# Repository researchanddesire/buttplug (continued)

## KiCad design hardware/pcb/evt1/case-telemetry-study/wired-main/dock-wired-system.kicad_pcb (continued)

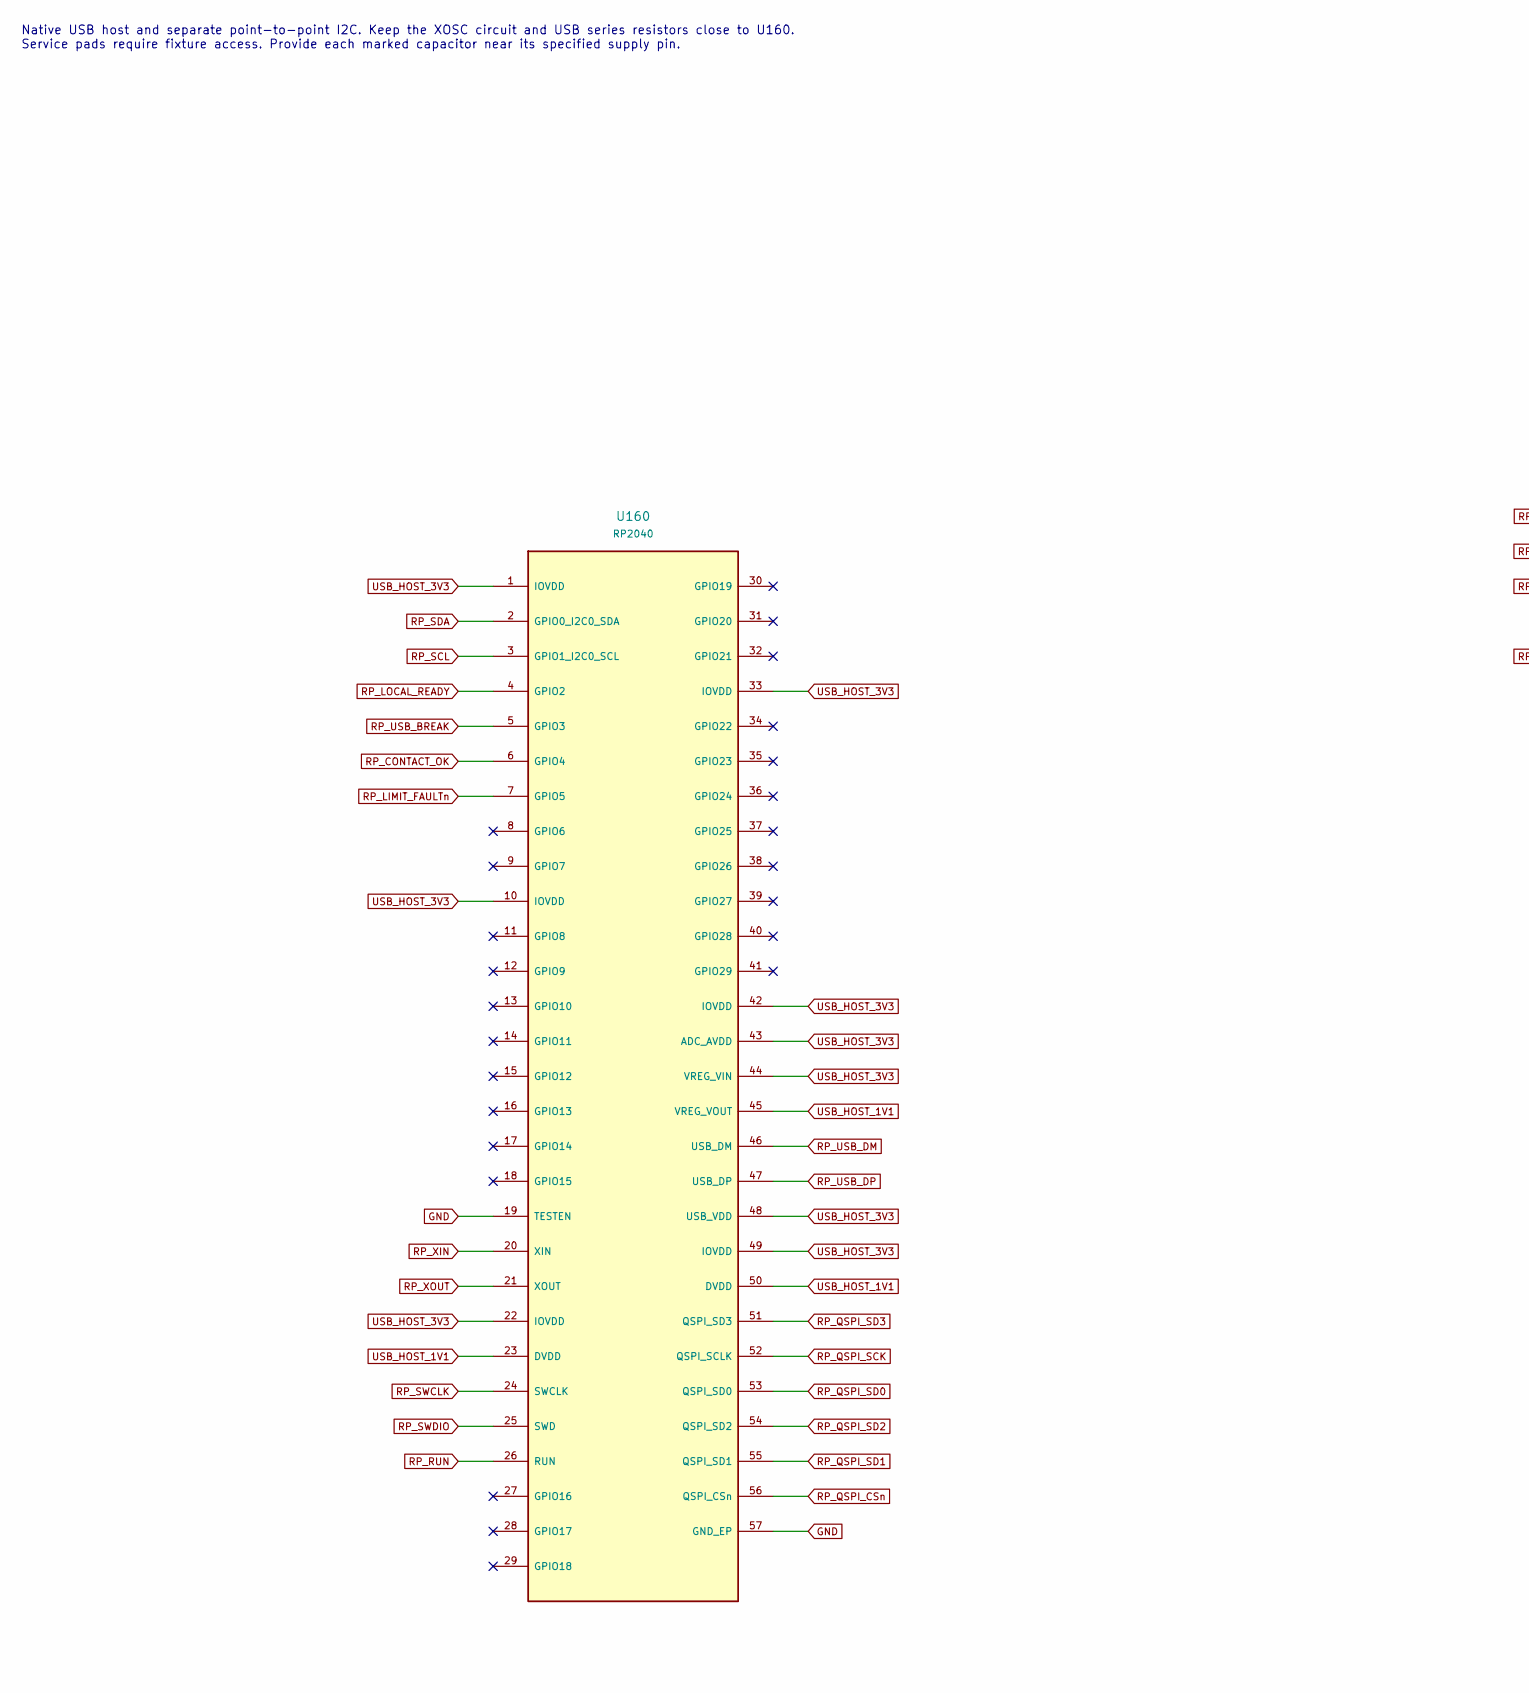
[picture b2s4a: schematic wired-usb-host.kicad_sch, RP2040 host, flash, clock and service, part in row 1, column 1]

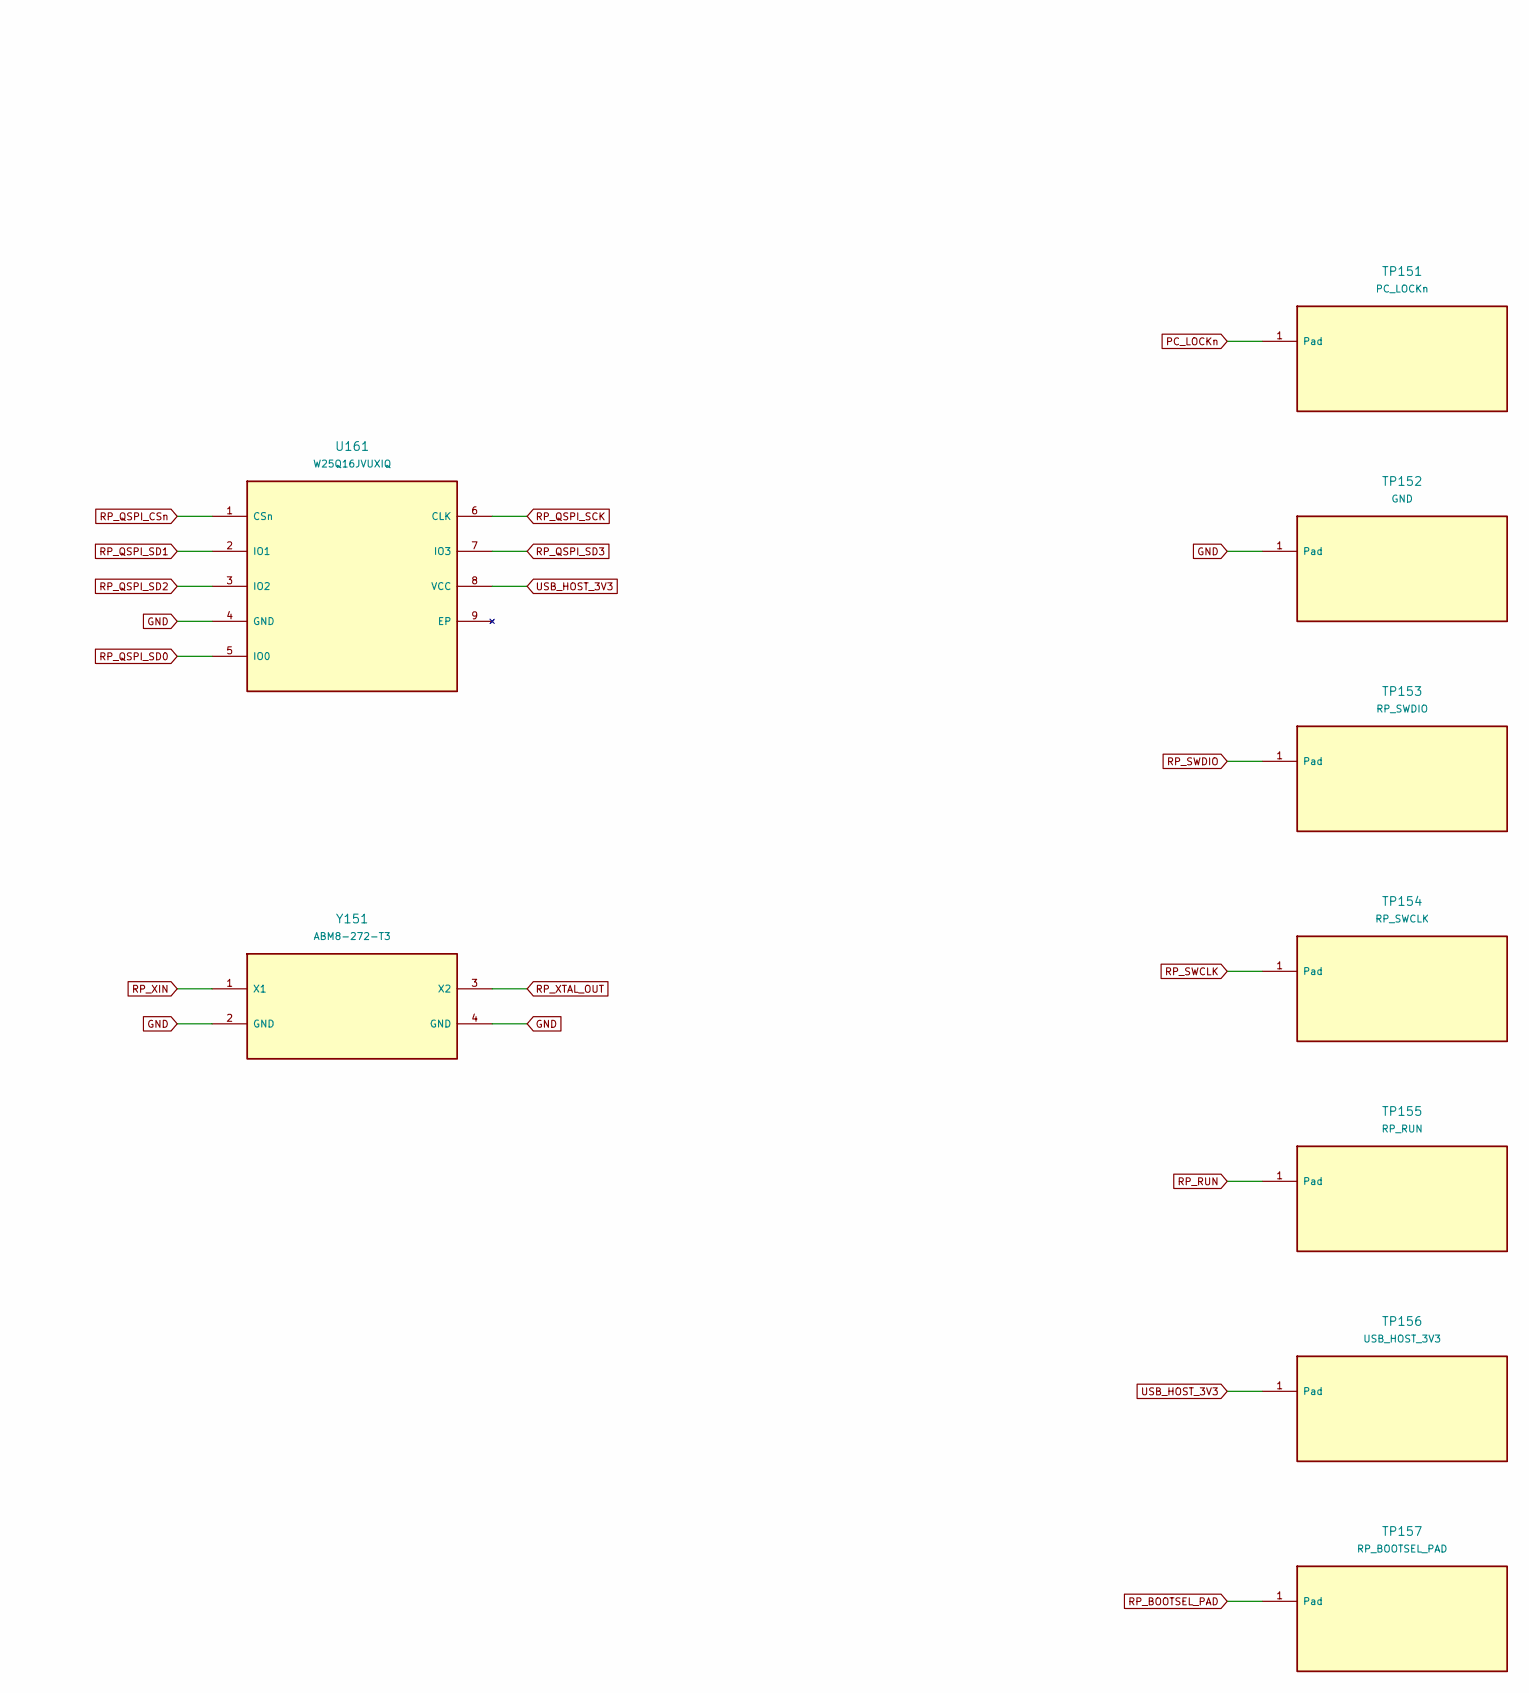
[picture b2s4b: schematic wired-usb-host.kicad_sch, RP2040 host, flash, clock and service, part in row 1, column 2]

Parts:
TP151: PC_LOCKn; TestPoint_Pad_D1.5mm
TP152: GND; TestPoint_Pad_D1.5mm
TP153: RP_SWDIO; TestPoint_Pad_D1.5mm
TP154: RP_SWCLK; TestPoint_Pad_D1.5mm
TP155: RP_RUN; TestPoint_Pad_D1.5mm
TP156: USB_HOST_3V3; TestPoint_Pad_D1.5mm
TP157: RP_BOOTSEL_PAD; TestPoint_Pad_D1.5mm
U160: RP2040; QFN-56-1EP_7x7mm_P0.4mm_EP3.2x3.2mm; MPN RP2040
U161: W25Q16JVUXIQ; Winbond_USON-8_2x3mm_P0.5mm_UX; MPN W25Q16JVUXIQ
Y151: ABM8-272-T3; Crystal_SMD_3225-4Pin_3.2x2.5mm; MPN ABM8-272-T3

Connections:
GND: TP152.1, U160.19 (TESTEN), U160.57 (GND_EP), U161.4 (GND), Y151.2 (GND), Y151.4 (GND); also elsewhere on the board
PC_LOCKn: TP151.1; also elsewhere on the board
RP_BOOTSEL_PAD: TP157.1; also elsewhere on the board
RP_CONTACT_OK: U160.6 (GPIO4); also elsewhere on the board
RP_LIMIT_FAULTn: U160.7 (GPIO5); also elsewhere on the board
RP_LOCAL_READY: U160.4 (GPIO2); also elsewhere on the board
RP_QSPI_CSn: U160.56 (QSPI_CSn), U161.1 (CSn); also elsewhere on the board
RP_QSPI_SCK: U160.52 (QSPI_SCLK), U161.6 (CLK)
RP_QSPI_SD0: U160.53 (QSPI_SD0), U161.5 (IO0)
RP_QSPI_SD1: U160.55 (QSPI_SD1), U161.2 (IO1)
RP_QSPI_SD2: U160.54 (QSPI_SD2), U161.3 (IO2)
RP_QSPI_SD3: U160.51 (QSPI_SD3), U161.7 (IO3)
RP_RUN: TP155.1, U160.26 (RUN); also elsewhere on the board
RP_SCL: U160.3 (GPIO1_I2C0_SCL); also elsewhere on the board
RP_SDA: U160.2 (GPIO0_I2C0_SDA); also elsewhere on the board
RP_SWCLK: TP154.1, U160.24 (SWCLK)
RP_SWDIO: TP153.1, U160.25 (SWD)
RP_USB_BREAK: U160.5 (GPIO3); also elsewhere on the board
RP_USB_DM: U160.46 (USB_DM); also elsewhere on the board
RP_USB_DP: U160.47 (USB_DP); also elsewhere on the board
RP_XIN: U160.20 (XIN), Y151.1 (X1); also elsewhere on the board
RP_XOUT: U160.21 (XOUT); also elsewhere on the board
RP_XTAL_OUT: Y151.3 (X2); also elsewhere on the board
USB_HOST_1V1: U160.23 (DVDD), U160.45 (VREG_VOUT), U160.50 (DVDD); also elsewhere on the board
USB_HOST_3V3: TP156.1, U160.1 (IOVDD), U160.10 (IOVDD), U160.22 (IOVDD), U160.33 (IOVDD), U160.42 (IOVDD), U160.43 (ADC_AVDD), U160.44 (VREG_VIN), U160.48 (USB_VDD), U160.49 (IOVDD), U161.8 (VCC); also elsewhere on the board

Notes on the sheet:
Native USB host and separate point-to-point I2C. Keep the XOSC circuit and USB series resistors close to U160. Service pads require fixture access. Provide each marked capacitor near its specified supply pin.

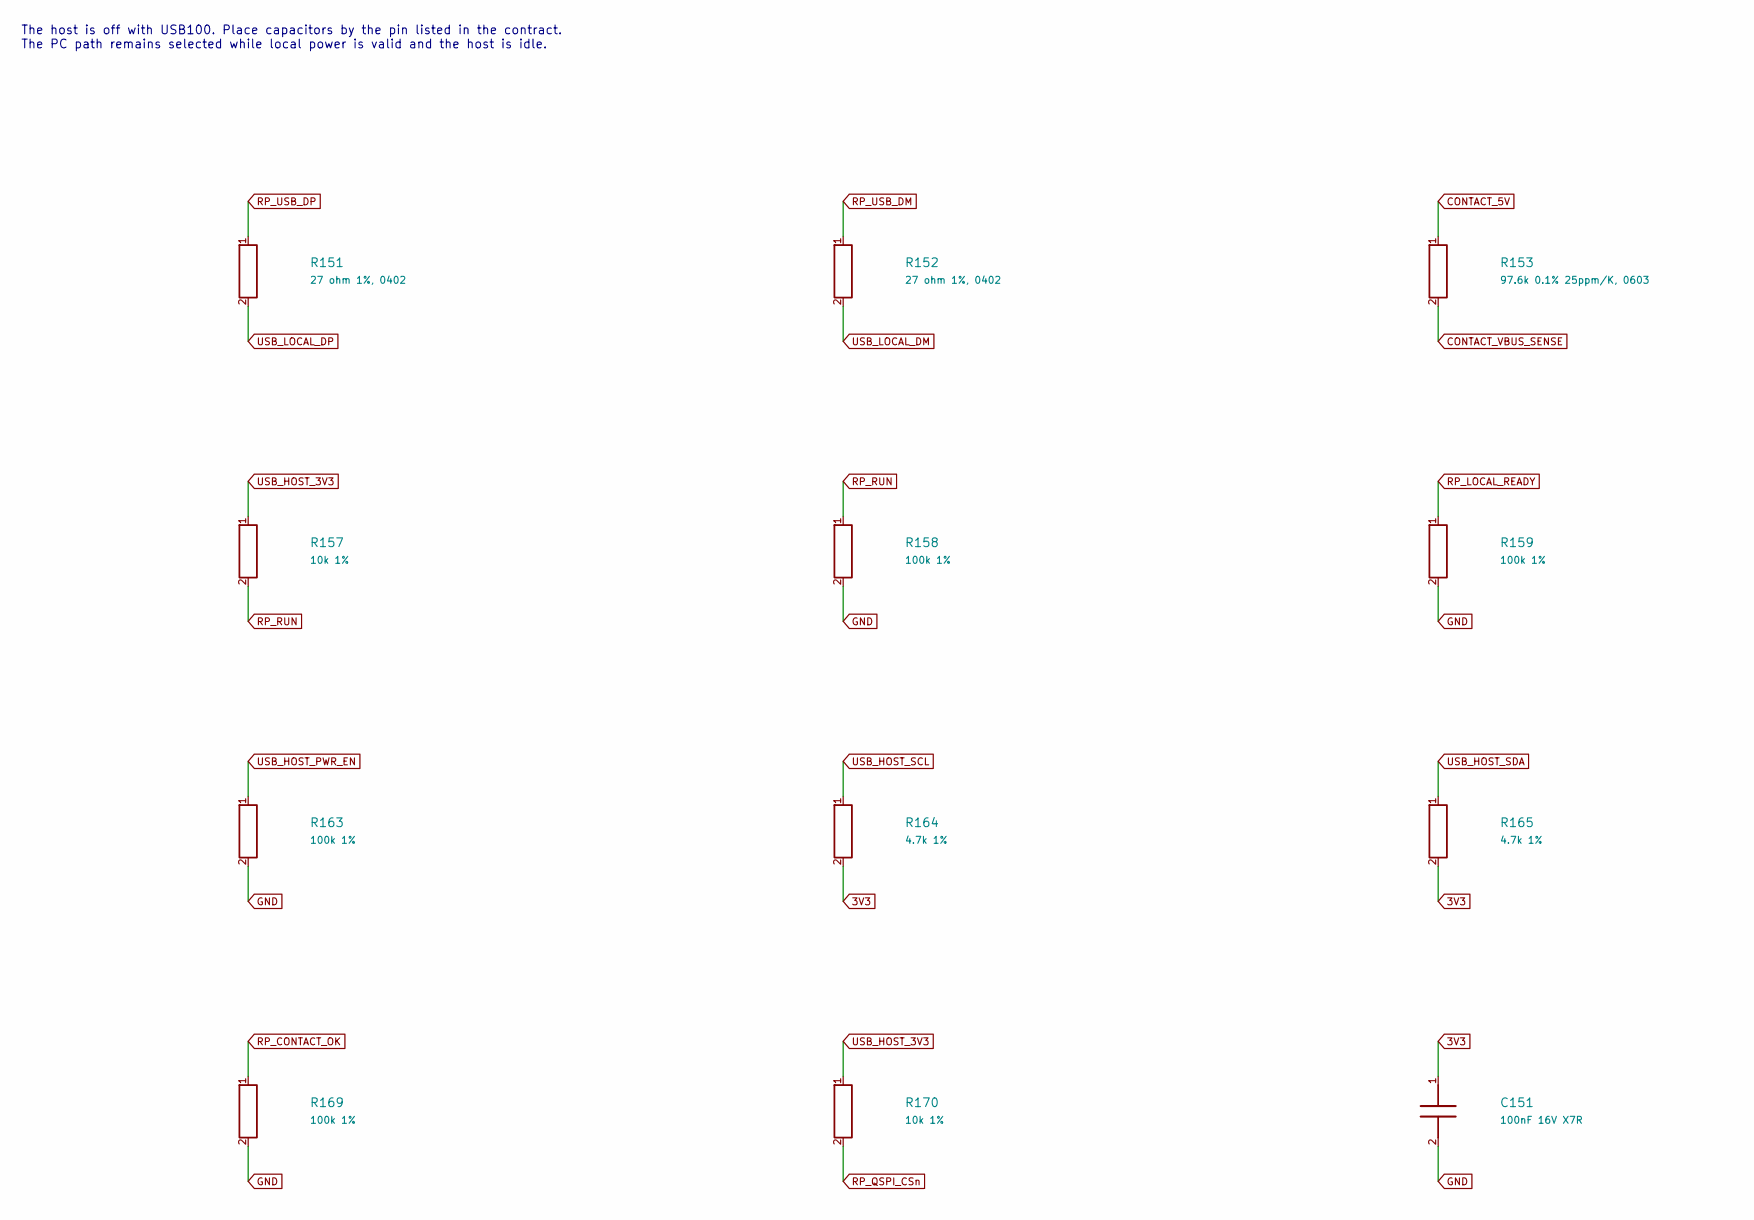
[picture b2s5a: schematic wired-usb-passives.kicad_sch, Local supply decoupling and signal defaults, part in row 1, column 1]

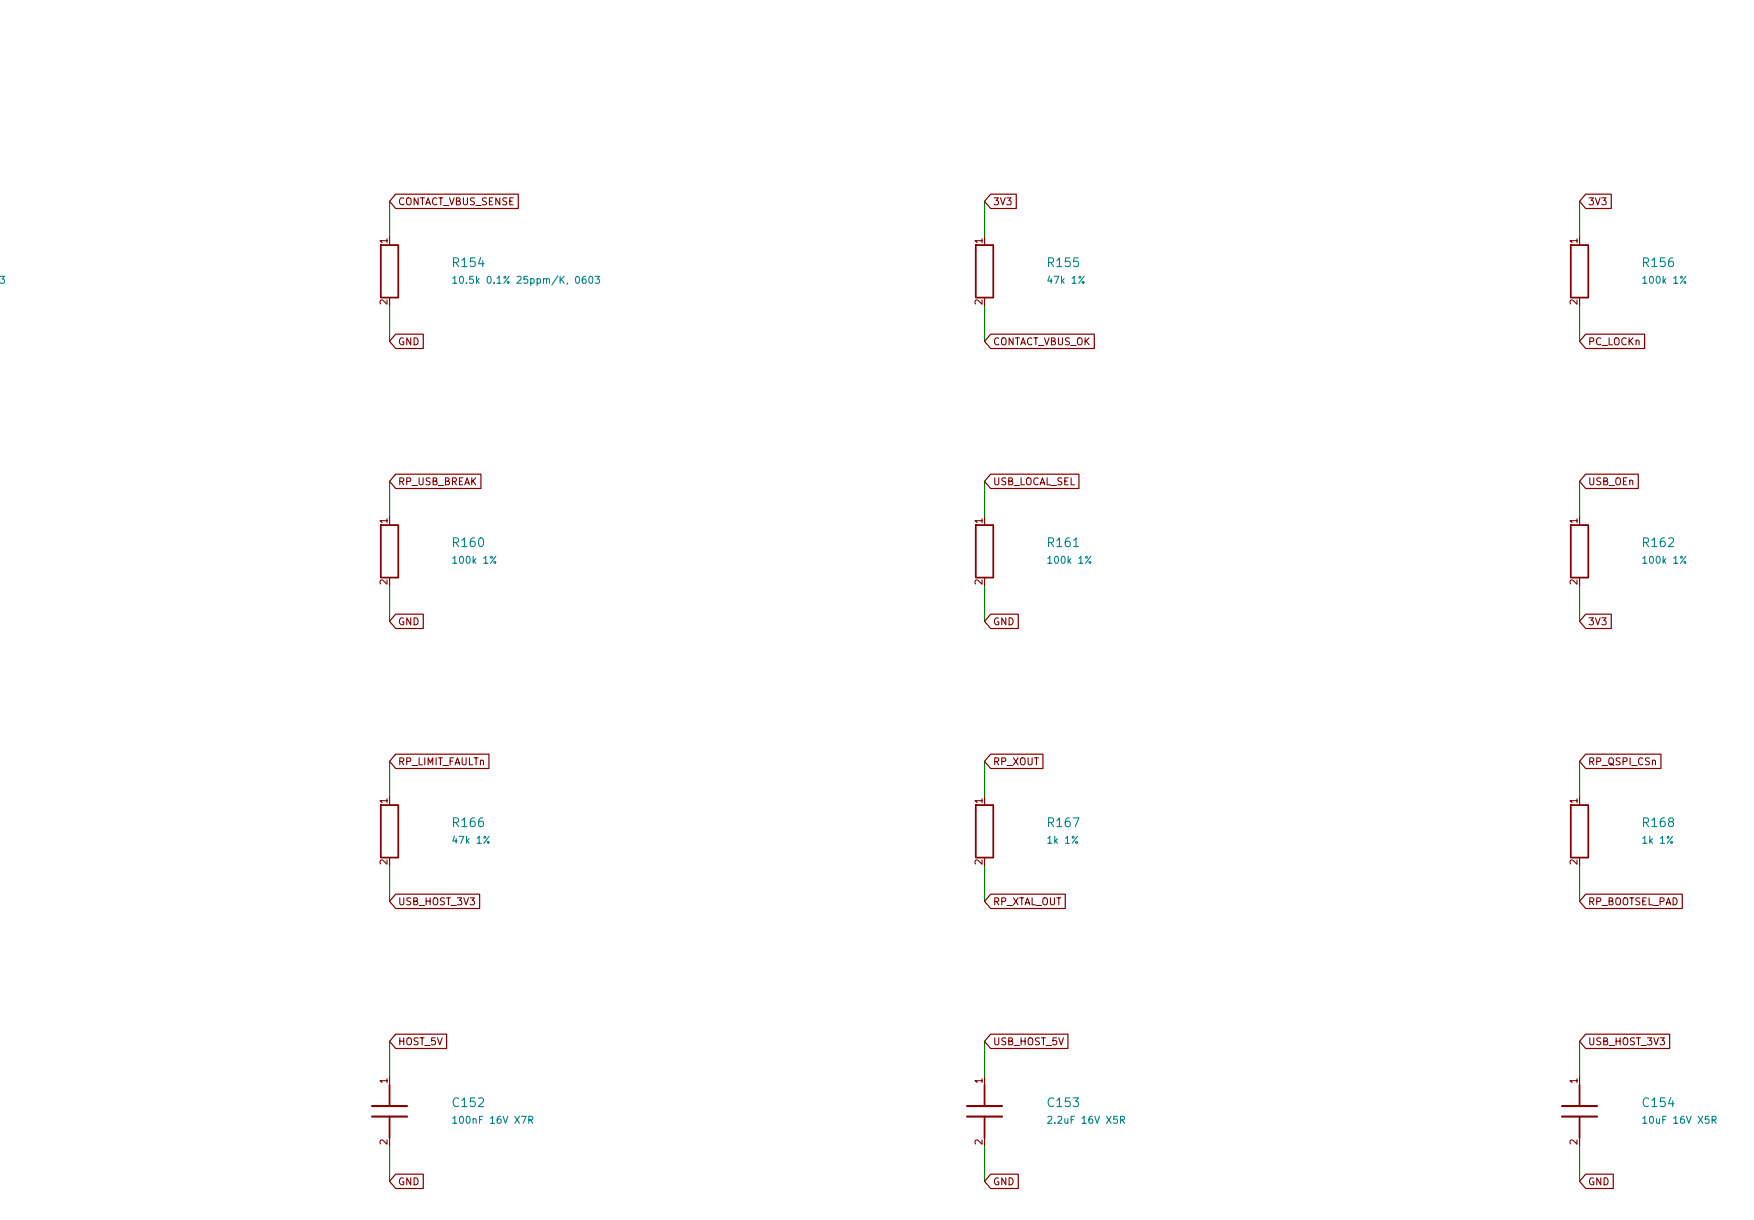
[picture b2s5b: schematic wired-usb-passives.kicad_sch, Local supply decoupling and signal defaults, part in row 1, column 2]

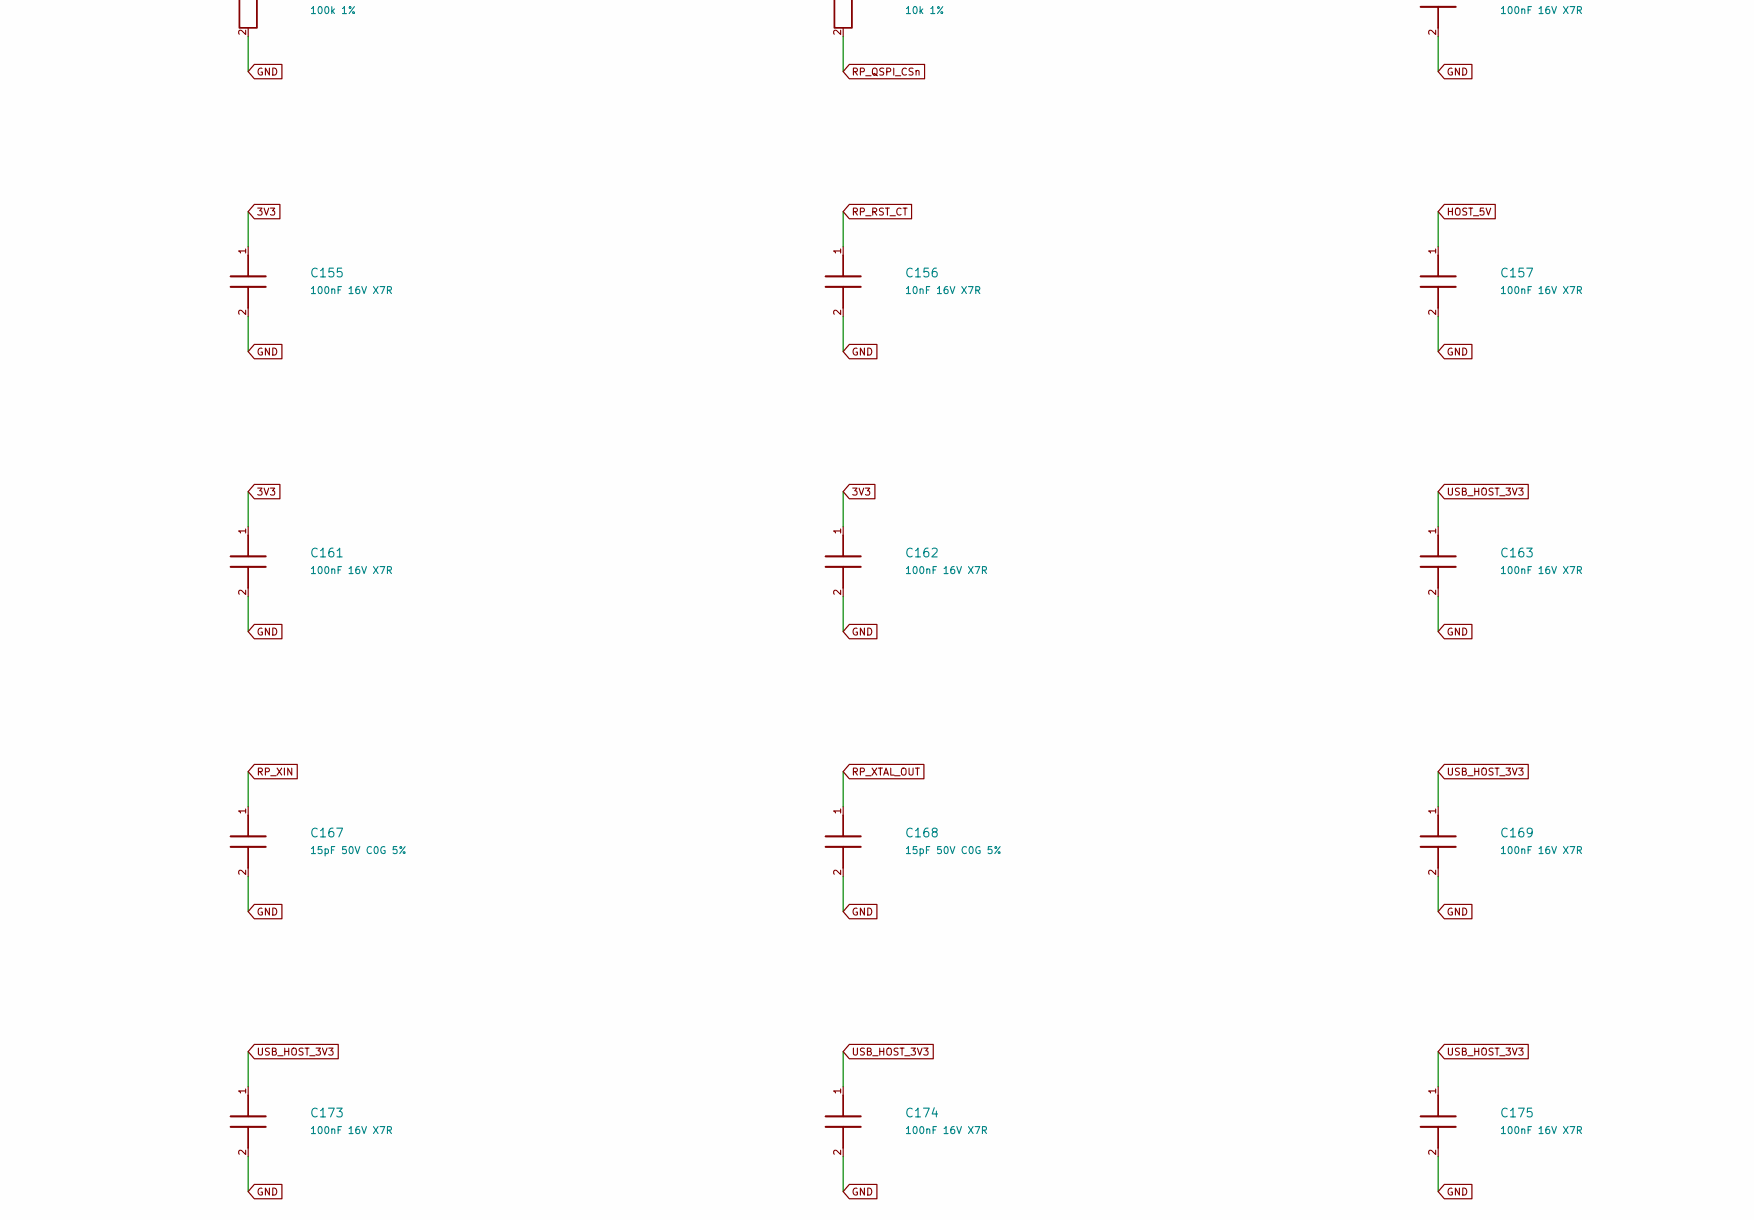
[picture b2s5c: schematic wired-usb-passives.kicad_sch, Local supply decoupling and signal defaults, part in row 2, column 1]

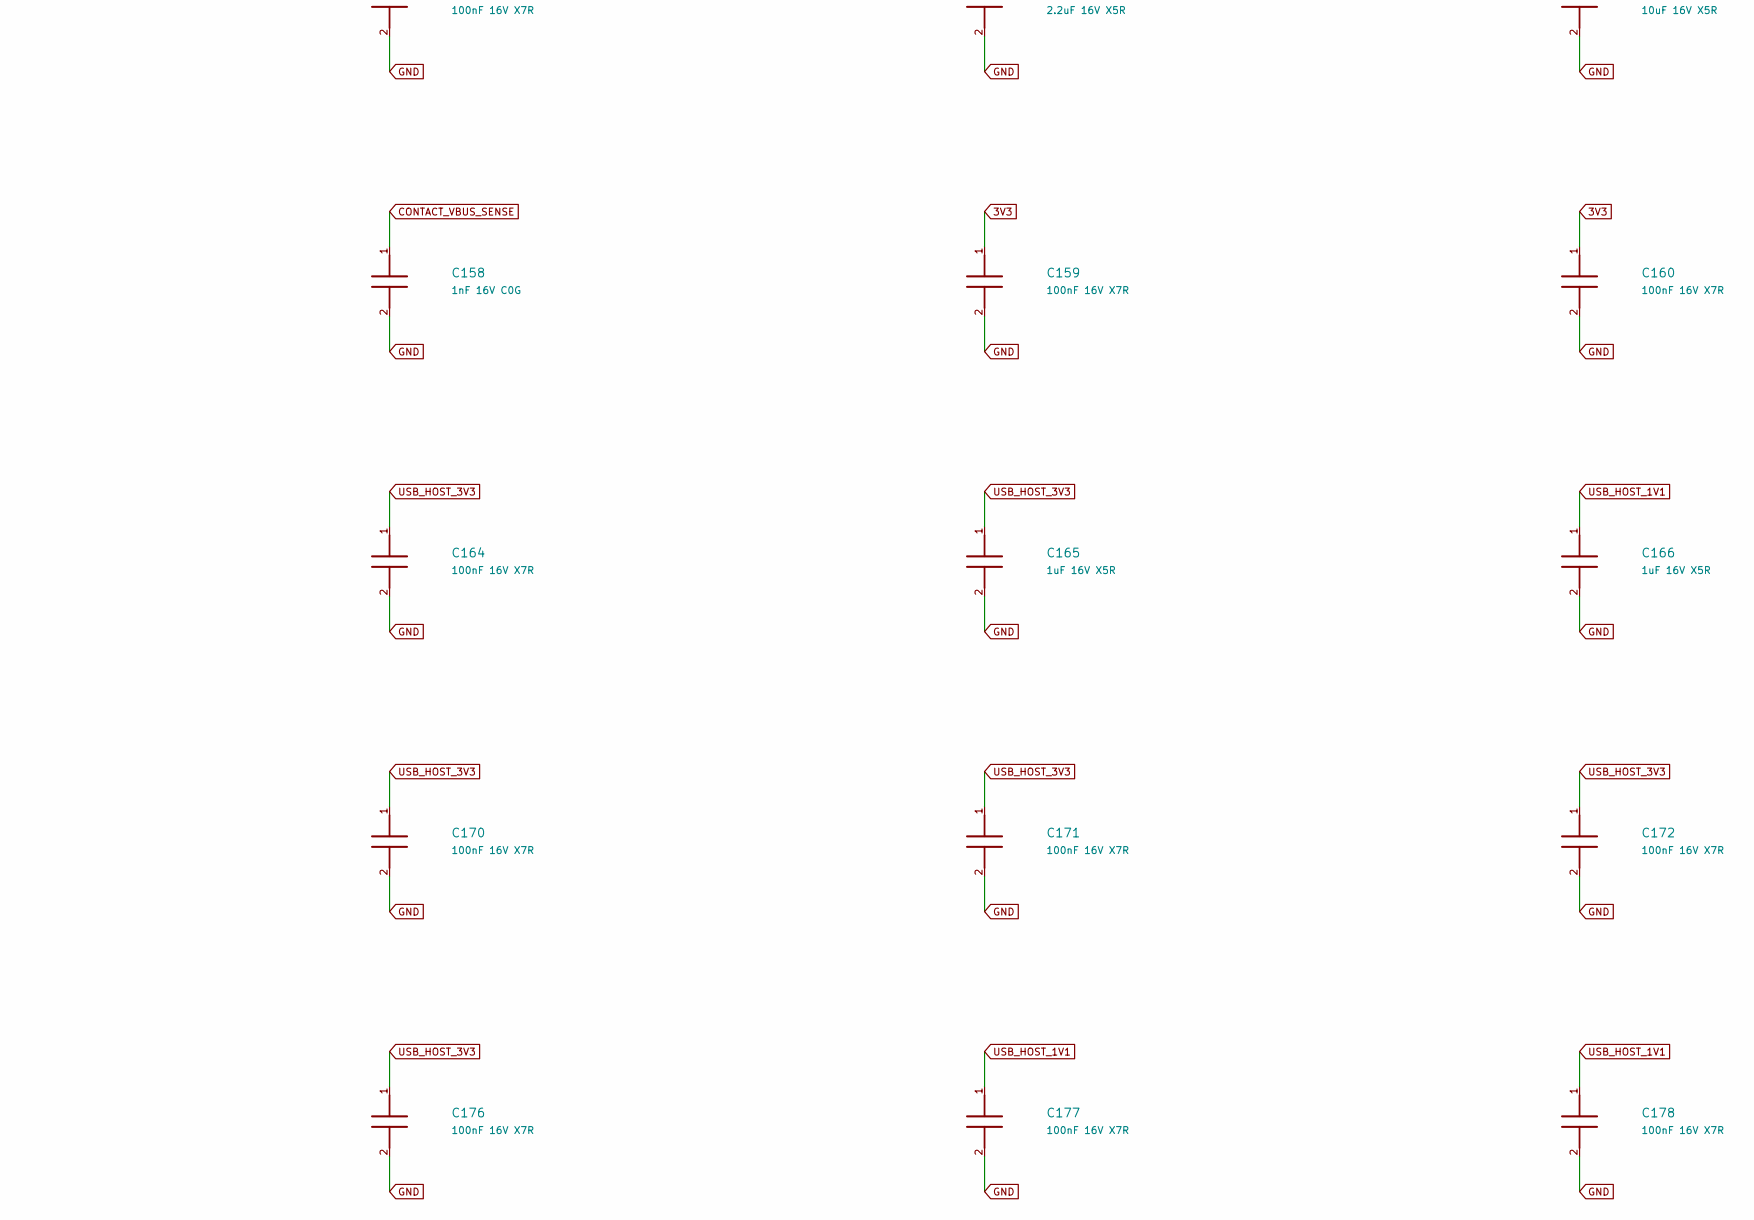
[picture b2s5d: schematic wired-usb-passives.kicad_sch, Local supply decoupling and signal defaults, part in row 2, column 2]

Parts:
C151, C152, C155, C157, C159, C160, C161, C162, C163, C164, C169, C170, C171, C172, C173, C174, C175, C176, C177, C178: 100nF 16V X7R; C_0402_1005Metric
C153: 2.2uF 16V X5R; C_0603_1608Metric
C154: 10uF 16V X5R; C_0805_2012Metric
C156: 10nF 16V X7R; C_0402_1005Metric
C158: 1nF 16V C0G; C_0402_1005Metric
C165, C166: 1uF 16V X5R; C_0603_1608Metric
C167, C168: 15pF 50V C0G 5%; C_0402_1005Metric
R151, R152: 27 ohm 1%, 0402; R_0402_1005Metric
R153: 97.6k 0.1% 25ppm/K, 0603; R_0603_1608Metric
R154: 10.5k 0.1% 25ppm/K, 0603; R_0603_1608Metric
R155, R166: 47k 1%; R_0402_1005Metric
R156, R158, R159, R160, R161, R162, R163, R169: 100k 1%; R_0402_1005Metric
R157, R170: 10k 1%; R_0402_1005Metric
R164, R165: 4.7k 1%; R_0402_1005Metric
R167, R168: 1k 1%; R_0402_1005Metric

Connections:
3V3: C151.1, C155.1, C159.1, C160.1, C161.1, C162.1, R155.1, R156.1, R162.2, R164.2, R165.2; also elsewhere on the board
CONTACT_5V: R153.1; also elsewhere on the board
CONTACT_VBUS_OK: R155.2; also elsewhere on the board
CONTACT_VBUS_SENSE: C158.1, R153.2, R154.1; also elsewhere on the board
GND: C151.2, C152.2, C153.2, C154.2, C155.2, C156.2, C157.2, C158.2, C159.2, C160.2, C161.2, C162.2, C163.2, C164.2, C165.2, C166.2, C167.2, C168.2, C169.2, C170.2, C171.2, C172.2, C173.2, C174.2, C175.2, C176.2, C177.2, C178.2, R154.2, R158.2, R159.2, R160.2, R161.2, R163.2, R169.2; also elsewhere on the board
HOST_5V: C152.1, C157.1; also elsewhere on the board
PC_LOCKn: R156.2; also elsewhere on the board
RP_BOOTSEL_PAD: R168.2; also elsewhere on the board
RP_CONTACT_OK: R169.1; also elsewhere on the board
RP_LIMIT_FAULTn: R166.1; also elsewhere on the board
RP_LOCAL_READY: R159.1; also elsewhere on the board
RP_QSPI_CSn: R168.1, R170.2; also elsewhere on the board
RP_RST_CT: C156.1; also elsewhere on the board
RP_RUN: R157.2, R158.1; also elsewhere on the board
RP_USB_BREAK: R160.1; also elsewhere on the board
RP_USB_DM: R152.1; also elsewhere on the board
RP_USB_DP: R151.1; also elsewhere on the board
RP_XIN: C167.1; also elsewhere on the board
RP_XOUT: R167.1; also elsewhere on the board
RP_XTAL_OUT: C168.1, R167.2; also elsewhere on the board
USB_HOST_1V1: C166.1, C177.1, C178.1; also elsewhere on the board
USB_HOST_3V3: C154.1, C163.1, C164.1, C165.1, C169.1, C170.1, C171.1, C172.1, C173.1, C174.1, C175.1, C176.1, R157.1, R166.2, R170.1; also elsewhere on the board
USB_HOST_5V: C153.1; also elsewhere on the board
USB_HOST_PWR_EN: R163.1; also elsewhere on the board
USB_HOST_SCL: R164.1; also elsewhere on the board
USB_HOST_SDA: R165.1; also elsewhere on the board
USB_LOCAL_DM: R152.2; also elsewhere on the board
USB_LOCAL_DP: R151.2; also elsewhere on the board
USB_LOCAL_SEL: R161.1; also elsewhere on the board
USB_OEn: R162.1; also elsewhere on the board

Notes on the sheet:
The host is off with USB100. Place capacitors by the pin listed in the contract. The PC path remains selected while local power is valid and the host is idle.

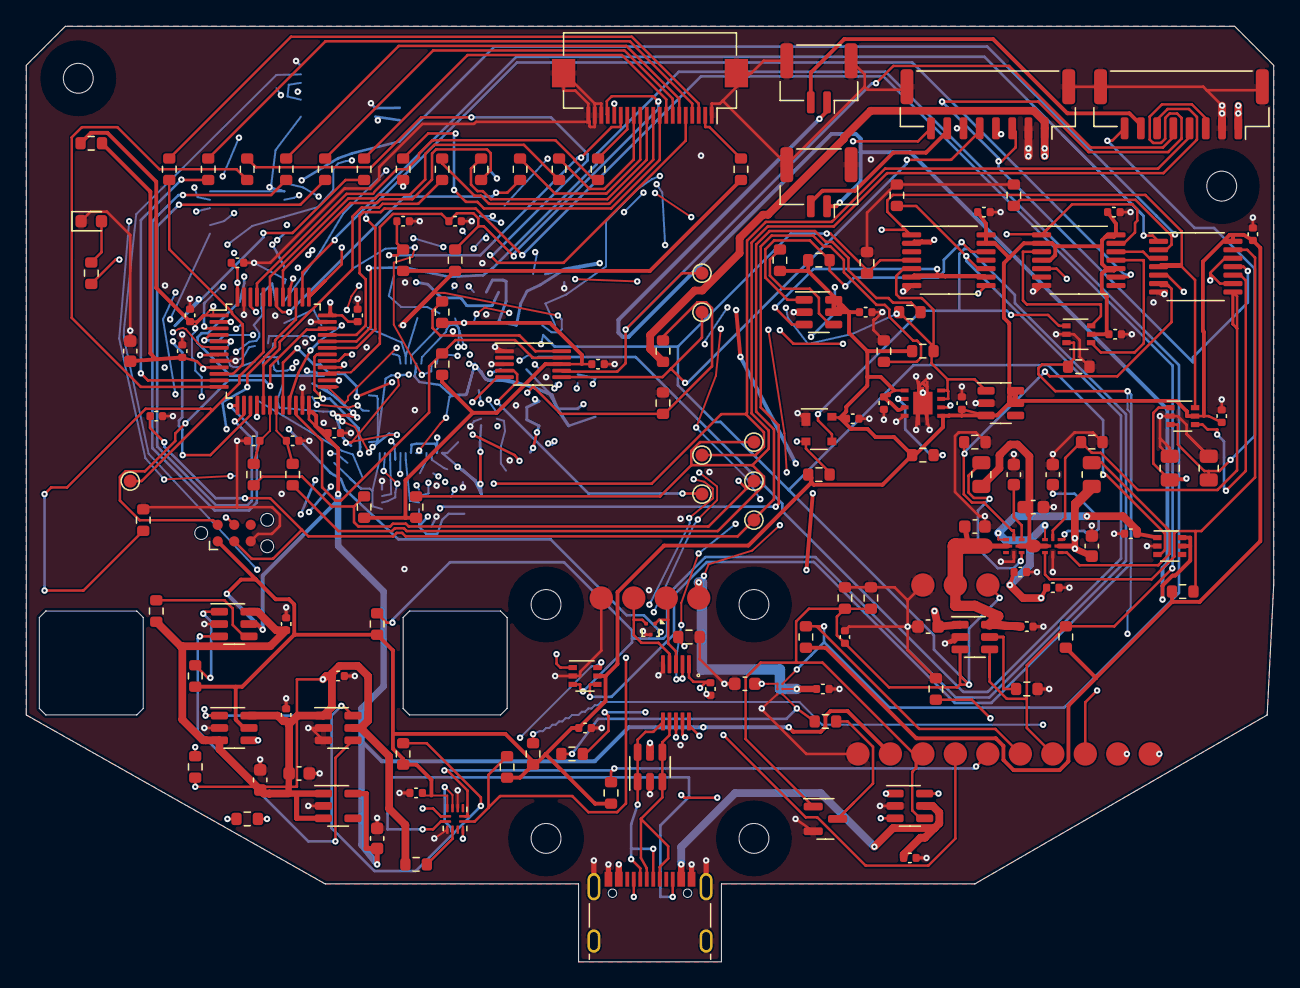
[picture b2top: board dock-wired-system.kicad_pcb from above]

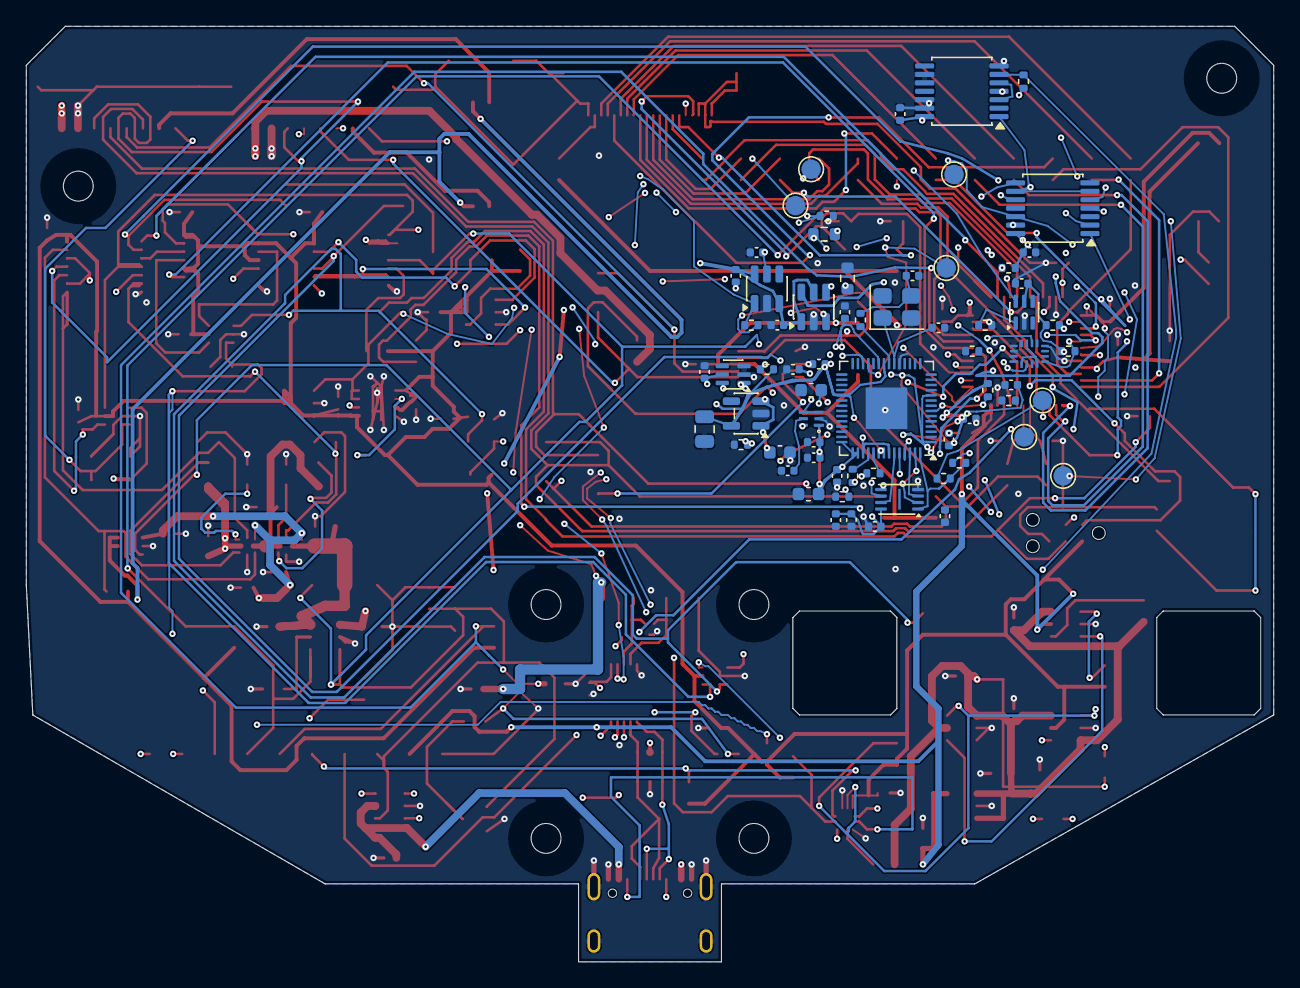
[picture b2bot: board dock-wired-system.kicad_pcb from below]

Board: 4 copper layers, 96.0 x 72.0 mm, 225 parts (66 on the bottom side), 148 nets.

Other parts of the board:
H701, H702, H703, H704, H705, H706: M2clearance2.3

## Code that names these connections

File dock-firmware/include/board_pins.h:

/* GPIO assignments bound to selected native MCU package. */
#ifndef DOCK_BOARD_PINS_H
#define DOCK_BOARD_PINS_H
#define BTN_CENTERn_DEBOUNCED_PORT GPIOB
#define BTN_CENTERn_DEBOUNCED_PIN 13u
#define BTN_LEFTn_PORT GPIOB
#define BTN_LEFTn_PIN 12u
#define BTN_RIGHTn_PORT GPIOB
#define BTN_RIGHTn_PIN 14u
#define CC_OUT1_PORT GPIOB
#define CC_OUT1_PIN 3u
#define CC_OUT2_PORT GPIOB
#define CC_OUT2_PIN 4u
#define DEVICE_LIMIT_FAULTn_PORT GPIOA
#define DEVICE_LIMIT_FAULTn_PIN 11u
#define LCD_A0_PORT GPIOB
#define LCD_A0_PIN 5u
#define LCD_CSn_PORT GPIOB
#define LCD_CSn_PIN 7u
#define LCD_DB0_PORT GPIOA
#define LCD_DB0_PIN 0u
#define LCD_DB1_PORT GPIOA
#define LCD_DB1_PIN 1u
#define LCD_DB2_PORT GPIOA
#define LCD_DB2_PIN 2u
#define LCD_DB3_PORT GPIOA
#define LCD_DB3_PIN 3u
#define LCD_DB4_PORT GPIOA
#define LCD_DB4_PIN 4u
#define LCD_DB5_PORT GPIOA
#define LCD_DB5_PIN 5u
#define LCD_DB6_PORT GPIOA
#define LCD_DB6_PIN 6u
#define LCD_DB7_PORT GPIOA
#define LCD_DB7_PIN 7u
#define LCD_RESETn_PORT GPIOB
#define LCD_RESETn_PIN 8u
#define LCD_WRn_PORT GPIOB
#define LCD_WRn_PIN 6u
#define LOOP_A_PORT GPIOC
#define LOOP_A_PIN 13u
#define LOOP_B_PORT GPIOC
#define LOOP_B_PIN 14u
#define MCU_ARM_PORT GPIOB
#define MCU_ARM_PIN 15u
#define MCU_STOPn_PORT GPIOA
#define MCU_STOPn_PIN 8u
#define MON_I2C_SCL_PORT GPIOB
#define MON_I2C_SCL_PIN 10u
#define MON_I2C_SDA_PORT GPIOB
#define MON_I2C_SDA_PIN 11u
#define NTC_BASE_PORT GPIOB
#define NTC_BASE_PIN 0u
#define NTC_LID_PORT GPIOB
#define NTC_LID_PIN 1u
#define RELEASE_SEEN_PORT GPIOA
#define RELEASE_SEEN_PIN 15u
#define SOURCE_OK_PORT GPIOC
#define SOURCE_OK_PIN 15u
#define STATUS_LED_PORT GPIOB
#define STATUS_LED_PIN 9u
#define SWCLK_PORT GPIOA
#define SWCLK_PIN 14u
#define SWDIO_PORT GPIOA
#define SWDIO_PIN 13u
#define UV_LIMIT_FAULTn_PORT GPIOA
#define UV_LIMIT_FAULTn_PIN 12u
#define UV_RUN_PORT GPIOA
#define UV_RUN_PIN 10u
#define UV_VBUS_MON_PORT GPIOB
#define UV_VBUS_MON_PIN 2u
#define WDI_PORT GPIOA
#define WDI_PIN 9u
#define NTC_BASE_ADC_CHANNEL 8u
#define NTC_LID_ADC_CHANNEL 9u
#endif

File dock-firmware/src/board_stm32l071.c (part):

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    uint32_t start=ticks;
    while ((uint32_t)(ticks-start)<ms) __WFI();
}
void board_lcd_reset(bool high) { write_pin(LCD_RESETn_PORT,LCD_RESETn_PIN,high); }
void board_lcd_write(bool data,uint8_t byte) {
    write_pin(LCD_CSn_PORT,LCD_CSn_PIN,false); write_pin(LCD_A0_PORT,LCD_A0_PIN,data);
    /* Only PA0..7 are touched. PA8 STOPn and PA9 WDI must be preserved. */
    LCD_DB0_PORT->BSRR=((uint32_t)(~byte&255u)<<16)|byte;
    board_delay_us(2); write_pin(LCD_WRn_PORT,LCD_WRn_PIN,false);
    board_delay_us(2); write_pin(LCD_WRn_PORT,LCD_WRn_PIN,true);
    board_delay_us(2); write_pin(LCD_CSn_PORT,LCD_CSn_PIN,true);
}
static bool wait_bits(volatile uint32_t *r,uint32_t bits,bool set,uint32_t timeout) {
    uint32_t start=ticks;
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bool board_init(void) {
    RCC->IOPENR|=RCC_IOPENR_GPIOAEN|RCC_IOPENR_GPIOBEN|RCC_IOPENR_GPIOCEN;
    (void)RCC->IOPENR;
    write_pin(MCU_STOPn_PORT,MCU_STOPn_PIN,false);write_pin(MCU_ARM_PORT,MCU_ARM_PIN,false);write_pin(WDI_PORT,WDI_PIN,false);
    mode(GPIOA,8,1);mode(GPIOB,15,1);mode(GPIOA,9,1);
    if(!clock_setup())return false;
    if(SysTick_Config(SystemCoreClock/1000u))return false;
    __enable_irq();
    for(unsigned j=0;j<8;++j)mode(GPIOA,j,1);
    for(unsigned j=10;j<13;++j)mode(GPIOA,j,0);
    mode(GPIOA,15,0); /* Preserve PA13/PA14 SWD reset settings. */
    mode(GPIOB,0,3);mode(GPIOB,1,3);
    for(unsigned j=2;j<5;++j)mode(GPIOB,j,0);
    for(unsigned j=5;j<10;++j)mode(GPIOB,j,1);
    for(unsigned j=12;j<15;++j)mode(GPIOB,j,0);
    for(unsigned j=13;j<16;++j)mode(GPIOC,j,0);
    write_pin(LCD_WRn_PORT,LCD_WRn_PIN,true);write_pin(LCD_CSn_PORT,LCD_CSn_PIN,true);write_pin(LCD_RESETn_PORT,LCD_RESETn_PIN,false);write_pin(STATUS_LED_PORT,STATUS_LED_PIN,false);
    for(unsigned j=10;j<=11;++j){mode(GPIOB,j,2);GPIOB->OTYPER|=1u<<j;
        GPIOB->AFR[1]=(GPIOB->AFR[1]&~(15u<<((j-8)*4)))|(6u<<((j-8)*4));}
    RCC->APB1ENR|=RCC_APB1ENR_I2C2EN;
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    uint16_t base,lid;
    if(!adc_read(NTC_BASE_ADC_CHANNEL,&base)||!adc_read(NTC_LID_ADC_CHANNEL,&lid)||!ads_service())return false;
    i->now_ms=ticks;
    i->left=button(&left_button,!read_pin(BTN_LEFTn_PORT,BTN_LEFTn_PIN));
    i->center=!read_pin(BTN_CENTERn_DEBOUNCED_PORT,BTN_CENTERn_DEBOUNCED_PIN); /* MAX6816 output, no second software debounce. */
    i->right=button(&right_button,!read_pin(BTN_RIGHTn_PORT,BTN_RIGHTn_PIN));
    i->loop_a=read_pin(LOOP_A_PORT,LOOP_A_PIN);i->loop_b=read_pin(LOOP_B_PORT,LOOP_B_PIN);i->source_ok=read_pin(SOURCE_OK_PORT,SOURCE_OK_PIN);
    i->uv_run=read_pin(UV_RUN_PORT,UV_RUN_PIN);i->release_seen=read_pin(RELEASE_SEEN_PORT,RELEASE_SEEN_PIN);
    i->device_limit_ok=read_pin(DEVICE_LIMIT_FAULTn_PORT,DEVICE_LIMIT_FAULTn_PIN);i->uv_limit_ok=read_pin(UV_LIMIT_FAULTn_PORT,UV_LIMIT_FAULTn_PIN);
    i->uv_vbus_present=read_pin(UV_VBUS_MON_PORT,UV_VBUS_MON_PIN);
    i->source=dock_decode_source(read_pin(CC_OUT1_PORT,CC_OUT1_PIN),read_pin(CC_OUT2_PORT,CC_OUT2_PIN));
    i->ntc_valid=dock_ntc_centi_c(base,&i->base_centi_c)&&dock_ntc_centi_c(lid,&i->lid_centi_c);
    i->monitor_valid=have_scan;i->monitor_ms=complete_scan_ms;
    i->base_uA=ads_values[0];i->lid_uA=ads_values[1];i->base_mV=ads_values[2];i->lid_mV=ads_values[3];
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void board_outputs(const dock_app *a) {
    /* Stop first on interruption; arm last on permission. Neither pin is a
       software UV-start strobe: hardware fresh CENTER clocks own UV_RUN. */
    if(!a->stop_n){write_pin(MCU_STOPn_PORT,MCU_STOPn_PIN,false);write_pin(MCU_ARM_PORT,MCU_ARM_PIN,false);}
    else {write_pin(MCU_ARM_PORT,MCU_ARM_PIN,a->arm);write_pin(MCU_STOPn_PORT,MCU_STOPn_PIN,true);}
    write_pin(STATUS_LED_PORT,STATUS_LED_PIN,a->led);
}
void board_watchdog_heartbeat(void) {
    /* TPS3431 responds to falling edges only. A toggle every loop would put
       two worst-case100ms loops between falling edges, exceeding170ms tWDmin.
       Complete one high/low pulse per successful loop instead. */
    write_pin(WDI_PORT,WDI_PIN,true);board_delay_us(2);write_pin(WDI_PORT,WDI_PIN,false);
}
void board_fail_stop(void) {
    write_pin(MCU_STOPn_PORT,MCU_STOPn_PIN,false);write_pin(MCU_ARM_PORT,MCU_ARM_PIN,false);
    __disable_irq();for(;;)__WFI(); /* External watchdog remains active. */
}

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
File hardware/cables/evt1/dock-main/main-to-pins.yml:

metadata:
  title: EVT1 dock Main to spring-pin PCB
  notes: Match pad numbers across the different PCB views.
    Pair USB D− and D+. Keep their exposed leads short. Use strain relief in the
    installed assembly and qualify USB operation on the received hardware.
options:
  fontname: Arial
  color_mode: FULL
connectors:
  J102:
    type: Dock Main front copper solder lands
    pins: [1, 2, 3, 4]
    pinlabels: [GND, PLUG_USB_DM, PLUG_USB_DP, CONTACT_5V]
    ignore_in_bom: true
  J94:
    type: Spring-pin PCB rear copper solder lands
    pins: [1, 2, 3, 4]
    pinlabels: [GND, DOCK_DM, DOCK_DP, DOCK_5V]
    ignore_in_bom: true
cables:
  DK:
    category: bundle
    type: Individually marked 28 AWG wire
    wirecount: 4
    colors: [BN, BN, BN, BN]
    wirelabels: [GND, D−, D+, 5V]
    gauge: 28
    gauge_unit: AWG
    length: 0.15
    length_unit: m
    manufacturer: Accu-Glass
    mpn: '100690'
    notes: Four 150 mm starting blanks. Trim to the fitted dock route.
      Use at least 4 mm centerline bend radius and inspect insulation OD at 0.60 mm maximum.
connections:
  - - J102: [1, 2, 3, 4]
    - DK: [1, 2, 3, 4]
    - J94: [1, 2, 3, 4]
